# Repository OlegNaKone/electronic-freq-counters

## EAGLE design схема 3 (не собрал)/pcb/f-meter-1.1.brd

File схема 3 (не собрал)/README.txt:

The AVR Attiny2313 Frequency Meter 1Hz - 10MHz, 1Hz step

Hardware and software: Pawe³ Kisielewski (manekinen)
manekinen@mdiy.pl

Compiler: bascom v.2.0.7.6  

PCB: Eagle light v.6.4.0        

Project website:  http://diy.elektroda.eu/miernik-czestotliwosci-na-avr-od-1hz-do-10mhz
English language: http://diy.elektroda.eu/miernik-czestotliwosci-na-avr-od-1hz-do-10mhz/?lang=en

Modifications allowed, do not remove this README from archive.
Do not remove info from pcb and code.

Any usage of this project in commercial/profit/sell purposes is prohibited.

Project related questions - post on the project site.

Private contact - manekinen@mdiy.pl

For software updates notifications, follow me at http://www.twitter.com/manekinen

24.03.2013

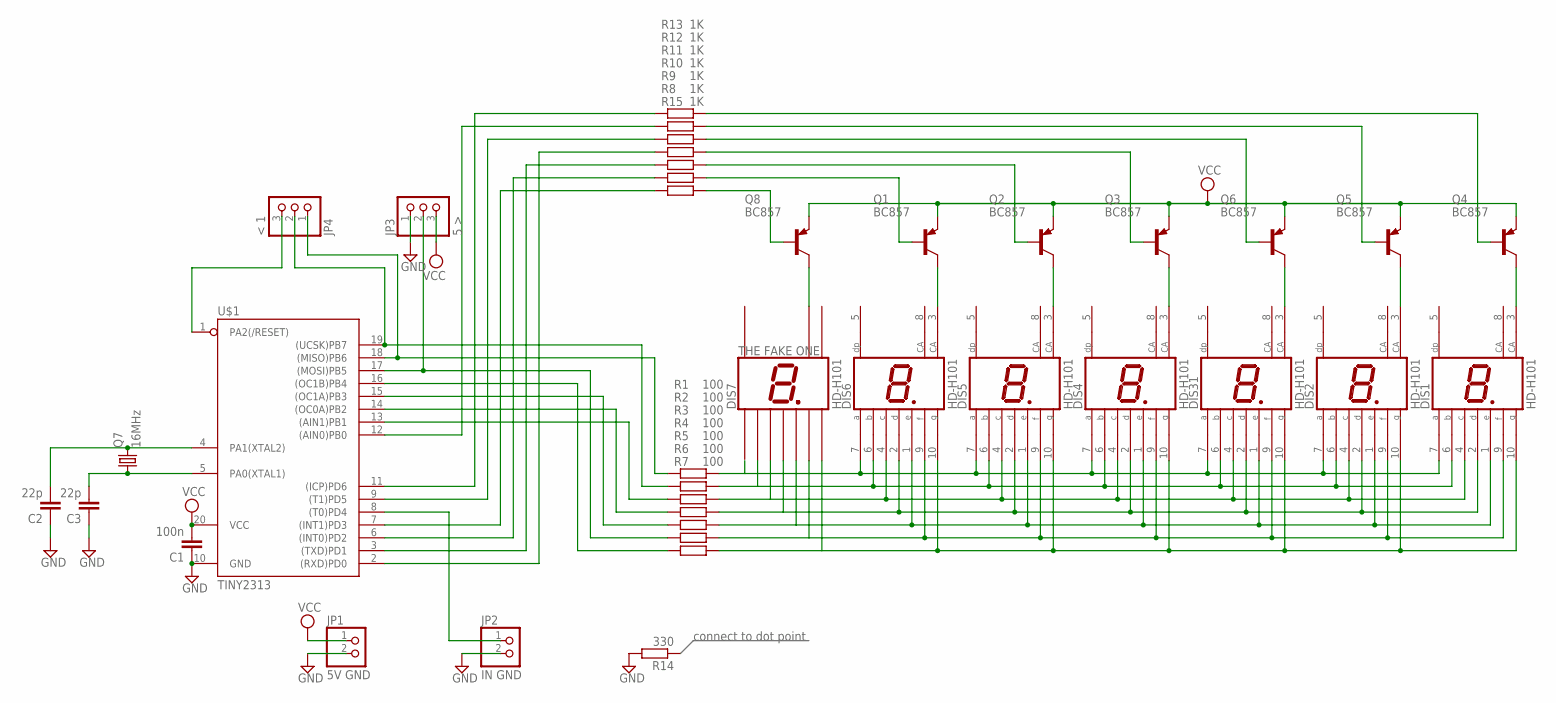
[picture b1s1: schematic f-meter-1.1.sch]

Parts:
C1: 100n; C0805
C2, C3: 22p; C0805
DIS1, DIS2, DIS4, DIS5, DIS6, DIS31: HD-H101; HDSP-M
JP1: 5V GND; 1X02
JP2: IN GND; 1X02
JP3: 5 >; 1X03SMD/90
JP4: < 1; 1X03SMD/90
Q1, Q2, Q3, Q4, Q5, Q6, Q8: BC857; SOT23-BEC
Q7: 16MHz; HC49/S
R1, R2, R3, R4, R5, R6, R7: 100; M0805
R8, R9, R10, R11, R12, R13, R15: 1K; M0805
R14: 330; M0805
U$1: TINY2313; SO20L$

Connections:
GND: C1.1, C2.1, C3.1, JP1.2, JP2.2, JP3.1, R14.2, U$1.10 (GND)
unnamed: C2.2, Q7.2, U$1.4 (PA1(XTAL2))
unnamed: C3.2, Q7.1, U$1.5 (PA0(XTAL1))
unnamed: DIS1.2 (D), DIS2.2 (D), DIS4.2 (D), DIS5.2 (D), DIS6.2 (D), DIS31.2 (D), R4.2
unnamed: DIS1.1 (E), DIS2.1 (E), DIS4.1 (E), DIS5.1 (E), DIS6.1 (E), DIS31.1 (E), R5.2
unnamed: DIS6.3 (CA), Q1.C
unnamed: DIS5.3 (CA), Q2.C
unnamed: DIS4.3 (CA), Q3.C
unnamed: DIS31.3 (CA), Q6.C
unnamed: DIS2.3 (CA), Q5.C
unnamed: DIS1.3 (CA), Q4.C
unnamed: Q1.B, R8.2
unnamed: Q2.B, R9.2
unnamed: Q3.B, R10.2
unnamed: Q6.B, R11.2
unnamed: Q5.B, R12.2
unnamed: Q4.B, R13.2
unnamed: R8.1, U$1.6 ((INT0)PD2)
unnamed: DIS1.9 (F), DIS2.9 (F), DIS4.9 (F), DIS5.9 (F), DIS6.9 (F), DIS31.9 (F), R6.2
unnamed: DIS1.7 (A), DIS2.7 (A), DIS4.7 (A), DIS5.7 (A), DIS6.7 (A), DIS31.7 (A), R1.2
unnamed: DIS1.6 (B), DIS2.6 (B), DIS4.6 (B), DIS5.6 (B), DIS6.6 (B), DIS31.6 (B), R2.2
unnamed: DIS1.4 (C), DIS2.4 (C), DIS4.4 (C), DIS5.4 (C), DIS6.4 (C), DIS31.4 (C), R3.2
unnamed: DIS1.10 (G), DIS2.10 (G), DIS4.10 (G), DIS5.10 (G), DIS6.10 (G), DIS31.10 (G), R7.2
unnamed: JP4.1, R1.1, U$1.18 ((MISO)PB6)
unnamed: JP4.3, U$1.1 (PA2(/RESET))
unnamed: Q8.B, R15.2
unnamed: R15.1, U$1.7 ((INT1)PD3)
unnamed: JP2.1, U$1.8 ((T0)PD4)
unnamed: R9.1, U$1.3 ((TXD)PD1)
unnamed: R10.1, U$1.2 ((RXD)PD0)
unnamed: R11.1, U$1.9 ((T1)PD5)
unnamed: R12.1, U$1.12 ((AIN0)PB0)
unnamed: R13.1, U$1.11 ((ICP)PD6)
unnamed: JP4.2, R2.1, U$1.19 ((UCSK)PB7)
unnamed: R3.1, U$1.13 ((AIN1)PB1)
unnamed: R4.1, U$1.14 ((OC0A)PB2)
unnamed: R5.1, U$1.15 ((OC1A)PB3)
unnamed: JP3.2, R6.1, U$1.17 ((MOSI)PB5)
unnamed: R7.1, U$1.16 ((OC1B)PB4)
VCC: C1.2, JP1.1, JP3.3, Q1.E, Q2.E, Q3.E, Q4.E, Q5.E, Q6.E, Q8.E, U$1.20 (VCC)

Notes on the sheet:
connect to dot point
HD-H101
DIS7
THE FAKE ONE

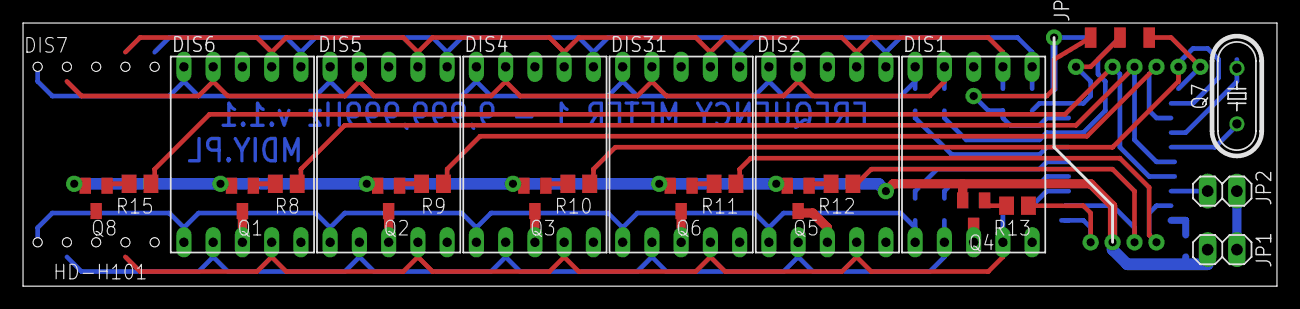
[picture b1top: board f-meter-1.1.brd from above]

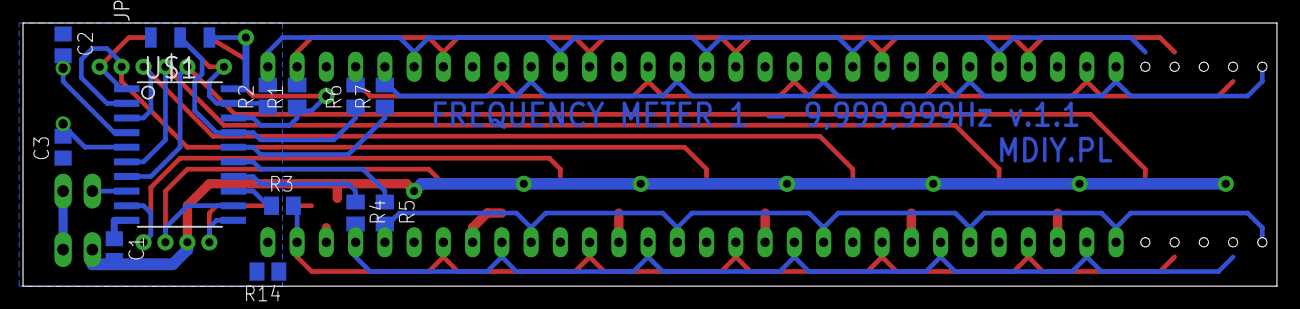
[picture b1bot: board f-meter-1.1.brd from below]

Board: 2 copper layers, 108.9 x 22.9 mm, 37 parts (13 on the bottom side), 40 nets.

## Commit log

2022-04-06 init
2022-04-06 added another circuit
